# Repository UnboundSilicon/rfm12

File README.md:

## Yet Another RFM12 Library?

So... the RFM12 is an old module.

Years ago I purchased a number of these, both the 433MHz and 915MHz versions, for various embedded projects, even going so far as to designing a few prototype PCBs around them. Like many of my hobby projects, they eventually found their way into a parts bin after little more than basic bring-up and proof-of-concept testing.  Let's just say that sometimes I prefer to learn how to use a module more than actually using the module in some type of project.

After recently moving into a new house, I've started planning several wireless projects for home automation, sensors, and other low-power devices, and for most projects, there's no reason why I couldn't use one of these modules.

My original code was written specifically for AVR microcontrollers, and like most existing RFM12 code, it's basically just a collection of functions that transmit 16-bit command words over SPI, hardcoded for a specific MCU. Add to that, the application is expected to understand register layouts, bit fields, and device-specific "magic numbers" in order to configure and use the radio. And then there's the lack of a proper API to abstract the register layout, bitfields, and SPI transactions.  Additionally, I plan on using STM32s and ESPs, in addition to AVRs, which would require a complete rewrite for each MCU.

That's where this project comes in.

The goal of my RFM12 Driver Library is to provide a modern, hardware independent, and well-documented C library that abstracts the device's low-level command interface into a clean, intuitive API. Instead of thinking in terms of register values and bit masks, the application should be able to think in terms of radio configuration, data transmission, and reception.

Details below 👇👇👇

## RFM12 Driver Library

A portable, hardware independent driver library for the HopeRF RFM12/RFM12B ISM-band transceiver modules.

## Goals

Most existing RFM12 code, including [HopeRF's own example code](datasheets/RFM12B_code.pdf), is tightly coupled to a specific microcontroller and consists primarily of functions that write 16-bit "magic number" command values to the SPI bus. This library takes a different approach.

The goal is to provide a clean, maintainable, and portable driver that:

* Separates radio logic from hardware-specific code
* Uses a Hardware Abstraction Layer (HAL) for portability
* Supports AVR, STM32, ESP32, and other microcontrollers
* Eliminates "magic numbers" from application code
* Provides a well-defined API for configuration and operation
* Allows multiple radio instances through a context-based design
* Supports both polling and interrupt-driven operation

## Design Philosophy

At its core, the RFM12 is simply a 16-bit SPI command/response device. Nearly every interaction with the radio consists of transmitting a 16-bit command word while some commands are simultaneously receiving a 16-bit status or data word. 

The application should configure the radio using meaningful functions and data structures, leaving the library responsible for encoding the appropriate bit fields and communicating with the hardware.

This:

```c
/* Traditional command-word interface */
WriteCMD(0x80D8);  /* FIFO and TX register enabled,
                      433 MHz band, 12.5 pF crystal load */
WriteCMD(0xA640);  /* 434.000 MHz */
WriteCMD(0xC647);  /* approximately 4,800 bit/s */
```

becomes this:

```c
/* Unbound Silicon RFM12 driver */
rfm12_set_tx_data_register_enable(radio, RFM12_ENABLE);
rfm12_set_rx_fifo_enable(radio, RFM12_ENABLE);
rfm12_set_frequency_band(radio, RFM12_BAND_433);
rfm12_set_xtal_cap(radio, RFM12_XTAL_CAP_12_5PF);

rfm12_set_frequency(radio, 434000000UL);
rfm12_set_data_rate(radio, RFM12_DATA_RATE_4800);

rfm12_apply_to_radio(radio);
```

The result is code that is much easier to read, easier to maintain, and easier to port to new hardware, while still exposing the full functionality of the RFM12 when needed.

## Key Features

* Portable C implementation
* Hardware abstraction layer
* Configurable SPI interface
* Suitable for polling or interrupt-driven applications
* Byte-level transmit and receive primitives
* Register and command abstraction
* Frequency, bitrate, and power configuration helpers
* FIFO management
* Support for multiple radio instances
* Minimal RAM footprint
* No dynamic memory allocation

## HAL-Based Design

The driver depends only on one user-provided function and an arbitrary context pointer:

```c
typedef RFM12_result_t (*RFM12_spi_transfer16_fn) (
    void *context, 
    uint16_t  tx_word, 
    uint16_t *rx_word
);
```
The SPI transfer function performs one complete 16-bit SPI transaction with the RFM12. It is responsible for any platform-specific operations required for that transaction, including selecting the RFM12, transferring the 16-bit `tx_word`, capturing the returned 16-bit word into `*rx_word`, and releasing the device.

The `context` pointer allows the application to associate platform-specific SPI information with a particular RFM12 instance. The driver does not interpret this pointer; it simply passes it unchanged to the SPI transfer function.

The application may use the context to identify whatever is required to communicate with that radio, such as:

* Which SPI peripheral to use
* Which GPIO pin controls the RFM12 chip select
* Platform-specific SPI or GPIO state
* A structure containing all hardware information associated with that radio

This allows the same HAL function to support multiple RFM12 modules or different hardware configurations without introducing platform-specific details into the driver itself.

The same library source code can run on:

* AVR ATmega devices
* STM32 devices
* ESP32 devices
* RP2040 devices
* Any platform with an SPI peripheral

## Context-Based API

Each radio instance is represented by a context structure.

```c
RFM12_t *radio;
```

The context stores:

* HAL callbacks
* Hardware-specific user data
* Current configuration
* Runtime state
* Driver status information

This approach allows multiple RFM12 modules to coexist in the same circuit / application while maintaining independent configuration and runtime state for each radio.

## Radio Instances

The driver uses a statically allocated pool and defaults to one radio instance.

To support additional radios, define `RFM12_NUM_RADIOS` when compiling `rfm12.c`:

    cc -DRFM12_NUM_RADIOS=2 -Iinclude -c src/rfm12.c

When all instances have been allocated, `rfm12_get_instance()` returns
`RFM12_ERROR_NO_INSTANCE_AVAILABLE`.

## Example Usage

```c

RFM12_t *radio;
RFM12_result_t result;

result = rfm12_get_instance(&radio);

if(result != RFM12_OK)
{
    handle_error(result);
}

result = rfm12_configure_hal(
    radio,
    my_spi_transfer16,
    &my_spi_context
);

if(result != RFM12_OK)
{
    handle_error(result);
}

rfm12_set_frequency_band(radio, RFM12_BAND_433);
rfm12_set_frequency(radio, 433920000UL);
rfm12_set_data_rate(radio, RFM12_DATA_RATE_4800);

result = rfm12_apply_to_radio(radio);

if(result != RFM12_OK)
{
    handle_error(result);
}

```

## Hardware Examples

The [PING/PONG example](examples/ping-pong/) demonstrates radio configuration and button-triggered message exchanges between two RFM12 modules. It shares the same application code across ATmega328P (Arduino Nano) and STM32F103C8 (Blue Pill) targets.

## Project Status

The RFM12 driver is under active development and hardware testing.

Current functionality includes:

* Platform-independent HAL interface
* Complete radio configuration and command encoding
* Staged configuration with explicit application to hardware
* Radio status decoding
* RX, TX, idle, standby, and sleep mode control
* FIFO-based receive operation
* TX register operation
* Software reset and synchronization control
* Multiple radio instance support
* Working hardware-tested PING/PONG communication

Development is currently focused on continued hardware validation, API refinement, testing, and documentation.

## License

This project is licensed under the BSD 3-Clause License. See [LICENSE](LICENSE) for details.

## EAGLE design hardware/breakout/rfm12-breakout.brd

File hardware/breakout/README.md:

# RFM12 Breakout Board

The schematic and PCB design files in this directory are licensed under
the BSD 3-Clause License. See the repository's [LICENSE](../../LICENSE)
file for details.

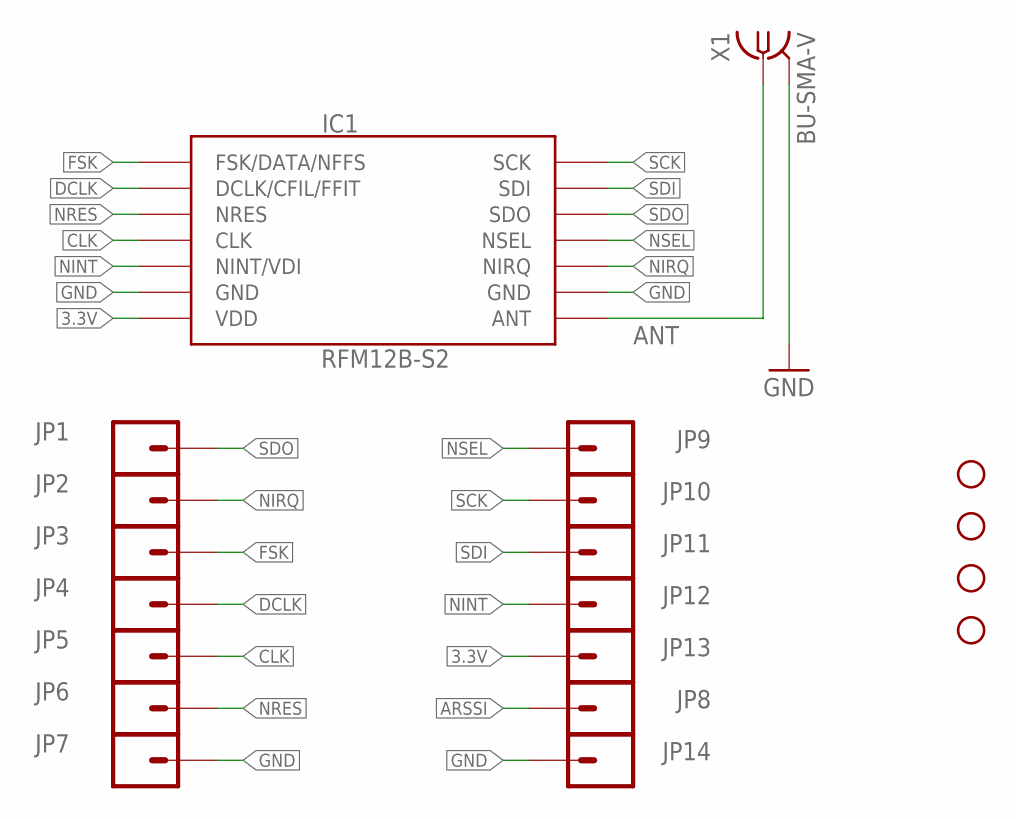
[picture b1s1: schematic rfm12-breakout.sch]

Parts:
IC1: RFM12B-S2
JP1, JP2, JP3, JP4, JP5, JP6, JP7, JP8, JP9, JP10, JP11, JP12, JP13, JP14: M01; 1X01
STANDOFF1, STANDOFF2, STANDOFF3, STANDOFF4: STAND-OFF
X1: BU-SMA-V

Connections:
3.3V: IC1.VDD, JP13.1
ANT: IC1.ANT, X1.1
ARSSI: JP8.1
CLK: IC1.CLK, JP5.1
DCLK: IC1.DCLK/CFIL/FFIT, JP4.1
FSK: IC1.FSK/DATA/NFFS, JP3.1
GND: IC1.GND@1 (GND), IC1.GND@2 (GND), JP7.1, JP14.1, X1.2, X1.3 (2), X1.4 (2), X1.5 (2)
NINT: IC1.NINT/VDI, JP12.1
NIRQ: IC1.NIRQ, JP2.1
NRES: IC1.NRES, JP6.1
NSEL: IC1.NSEL, JP9.1
SCK: IC1.SCK, JP10.1
SDI: IC1.SDI, JP11.1
SDO: IC1.SDO, JP1.1

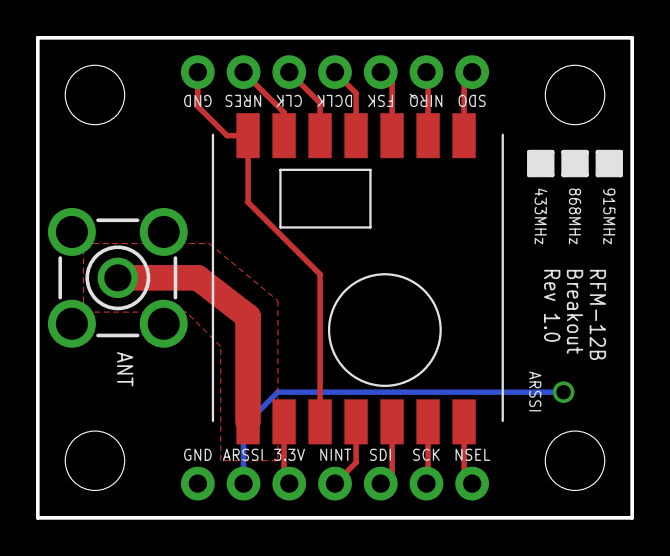
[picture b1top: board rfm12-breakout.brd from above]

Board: 2 copper layers, 33.0 x 26.7 mm, 20 parts (0 on the bottom side), 13 nets.

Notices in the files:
parts and their libraries:
SparkFun-Electromechanical: Licensing: CC v3.0 Share-Alike You are welcome to use this library for commercial purposes.
